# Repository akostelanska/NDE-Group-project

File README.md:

# NDE-Group-project
Repository for MPA-NDE Group Project

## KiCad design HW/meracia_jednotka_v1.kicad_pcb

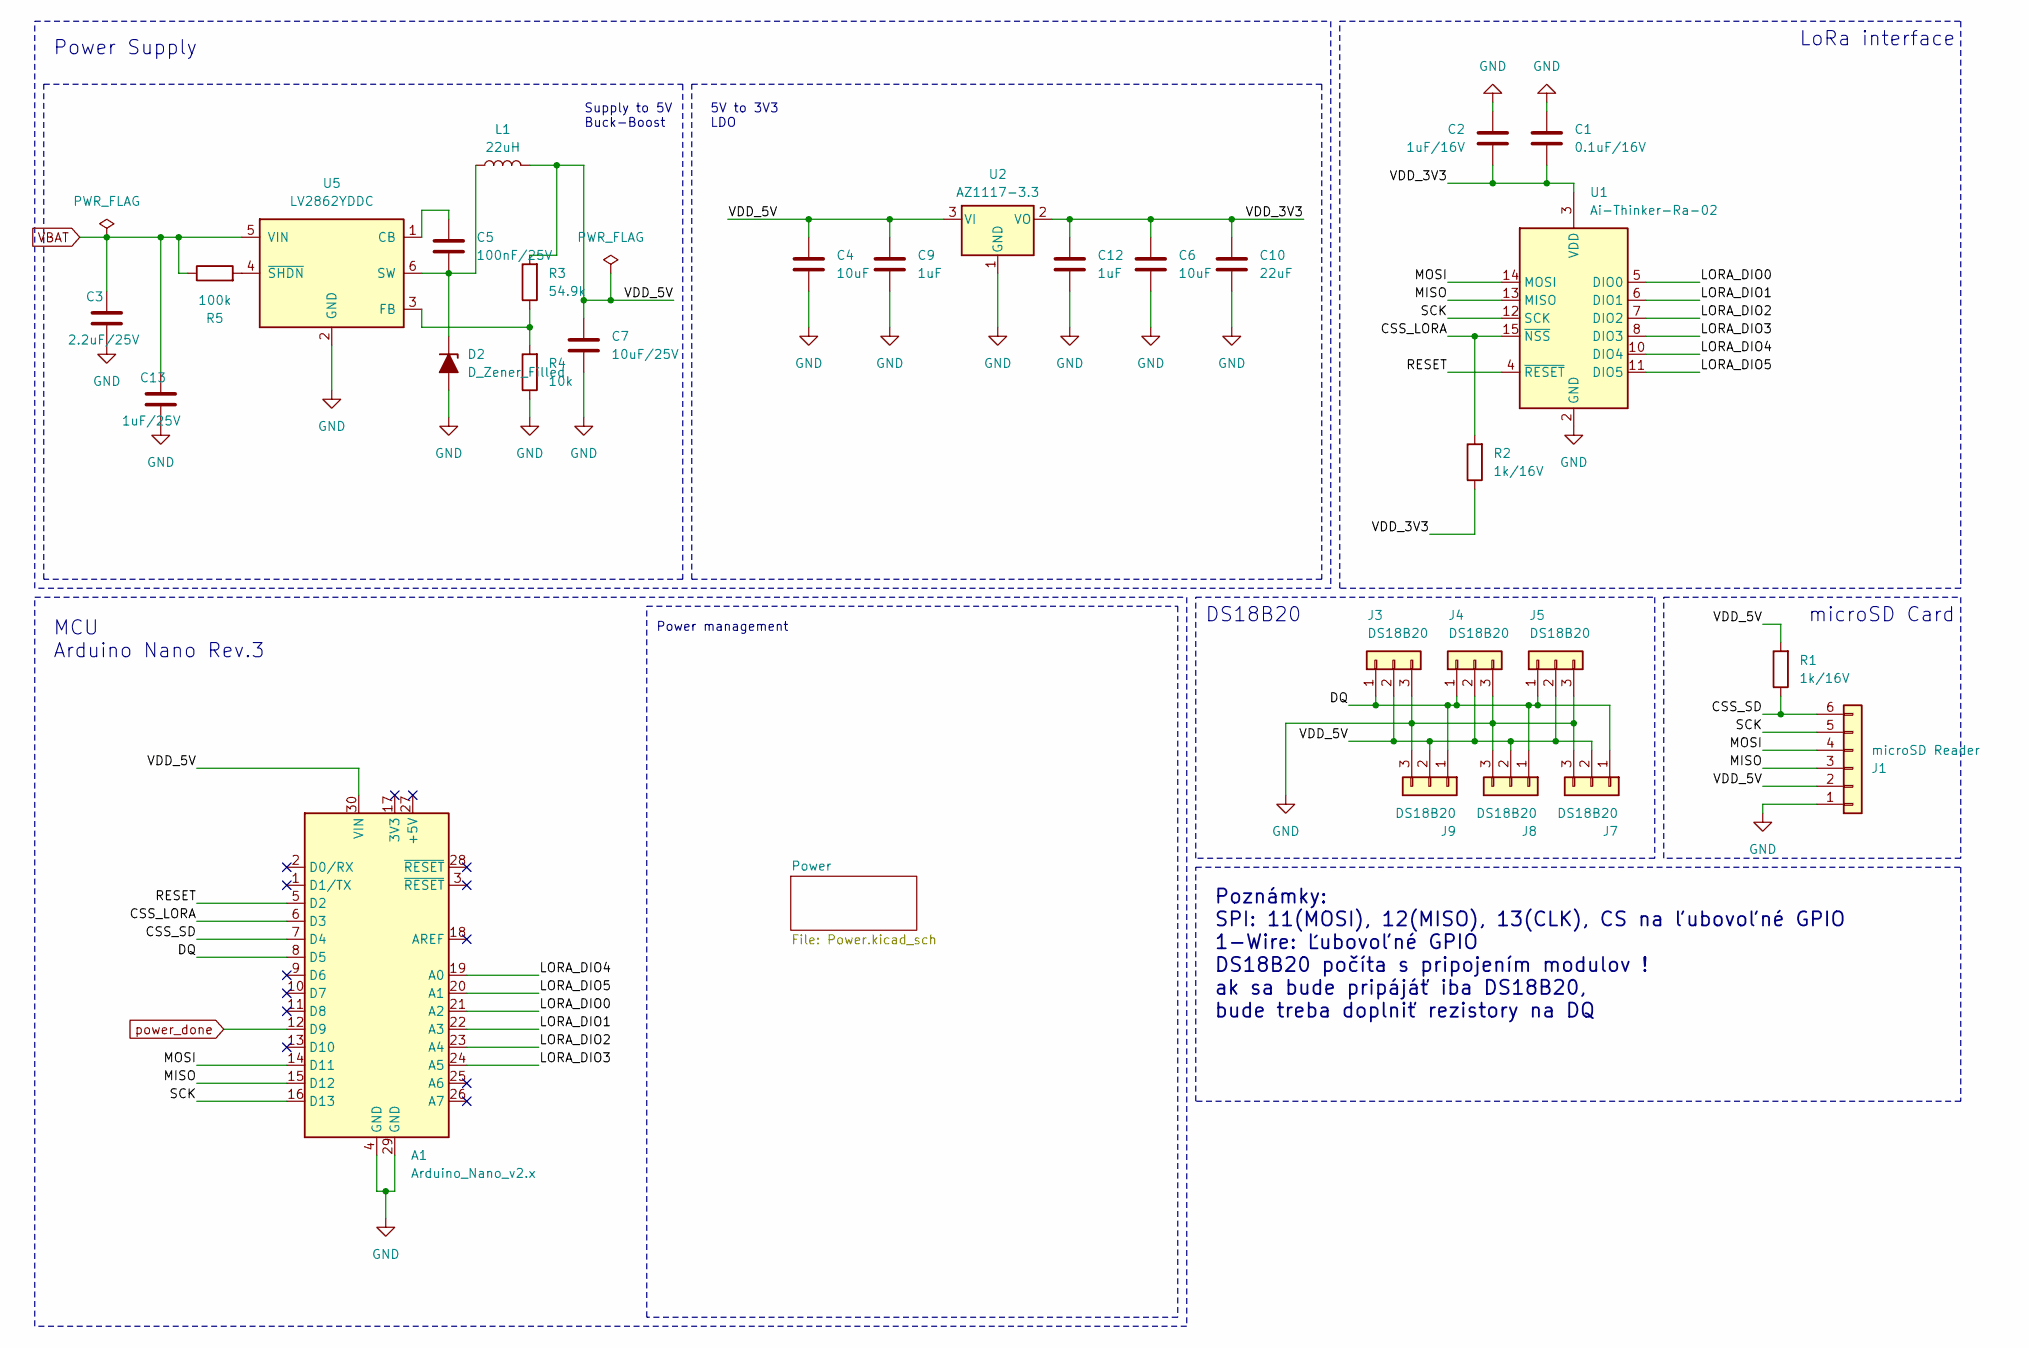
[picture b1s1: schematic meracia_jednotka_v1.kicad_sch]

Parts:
A1: Arduino_Nano_v2.x; Arduino_Nano
C1: 0.1uF/16V; C_1206_3216Metric_Pad1.33x1.80mm_HandSolder
C2: 1uF/16V; C_1206_3216Metric_Pad1.33x1.80mm_HandSolder
C3: 2.2uF/25V; C_1206_3216Metric_Pad1.33x1.80mm_HandSolder
C4, C6: 10uF; C_1206_3216Metric_Pad1.33x1.80mm_HandSolder
C5: 100nF/25V; C_1206_3216Metric_Pad1.33x1.80mm_HandSolder
C7: 10uF/25V; C_1206_3216Metric_Pad1.33x1.80mm_HandSolder
C9, C12: 1uF; C_0805_2012Metric_Pad1.18x1.45mm_HandSolder
C10: 22uF; C_1206_3216Metric_Pad1.33x1.80mm_HandSolder
C13: 1uF/25V; C_0805_2012Metric_Pad1.18x1.45mm_HandSolder
D2: D_Zener_Filled; D_1206_3216Metric_Pad1.42x1.75mm_HandSolder
J1: microSD Reader; PinHeader_1x06_P2.54mm_Vertical
J3, J4, J5, J7, J8, J9: DS18B20; PinHeader_1x03_P2.54mm_Vertical
L1: 22uH; L_Murata_LQH55DN_5.7x5.0mm
R1, R2: 1k/16V; R_1206_3216Metric_Pad1.30x1.75mm_HandSolder
R3: 54.9k; R_1206_3216Metric_Pad1.30x1.75mm_HandSolder
R4: 10k; R_1206_3216Metric_Pad1.30x1.75mm_HandSolder
R5: 100k; R_1206_3216Metric_Pad1.30x1.75mm_HandSolder
U1: Ai-Thinker-Ra-02; Ai-Thinker-Ra-01-LoRa
U2: AZ1117-3.3; SOT-223-3_TabPin2
U5: LV2862YDDC; SOT-23-6

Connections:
/CSS_LORA: A1.6 (D3), R2.2, U1.15 (~NSS)
/CSS_SD: A1.7 (D4), J1.6, R1.1
/DQ: A1.8 (D5), J3.1, J4.1, J5.1, J7.1, J8.1, J9.1
/LORA_DIO0: A1.21 (A2), U1.5 (DIO0)
/LORA_DIO1: A1.22 (A3), U1.6 (DIO1)
/LORA_DIO2: A1.23 (A4), U1.7 (DIO2)
/LORA_DIO3: A1.24 (A5), U1.8 (DIO3)
/LORA_DIO4: A1.19 (A0), U1.10 (DIO4)
/LORA_DIO5: A1.20 (A1), U1.11 (DIO5)
/MISO: A1.15 (D12), J1.3, U1.13 (MISO)
/MOSI: A1.14 (D11), J1.4, U1.14 (MOSI)
/RESET: A1.5 (D2), U1.4 (~RESET)
/SCK: A1.16 (D13), J1.5, U1.12 (SCK)
/VDD_3V3: C1.2, C2.2, C6.1, C10.1, C12.1, R2.1, U1.3 (VDD), U2.2 (VO)
/VDD_5V: A1.30 (VIN), C4.1, C7.1, C9.1, J1.2, J3.2, J4.2, J5.2, J7.2, J8.2, J9.2, L1.2, R1.2, R3.2, U2.3 (VI)
GND: A1.4 (GND), A1.29 (GND), C1.1, C2.1, C3.2, C4.2, C6.2, C7.2, C9.2, C10.2, C12.2, C13.2, D2.2 (A), J1.1, J3.3, J4.3, J5.3, J7.3, J8.3, J9.3, R4.1, U1.1 (GND), U1.2 (GND), U1.9 (GND), U1.16 (GND), U2.1 (GND), U5.2 (GND); also elsewhere on the board
unnamed: C5.2, D2.1 (K), L1.1, U5.6 (SW)
unnamed: C5.1, U5.1 (CB)
unnamed: R3.1, R4.2, U5.3 (FB)
unnamed: R5.2, U5.4 (~SHDN)
VBAT: C3.1, C13.1, R5.1, U5.5 (VIN); also elsewhere on the board
power_done: A1.12 (D9); also elsewhere on the board

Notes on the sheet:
5V to 3V3 LDO
Poznámky: SPI: 11(MOSI), 12(MISO), 13(CLK), CS na ľubovoľné GPIO 1-Wire: Ľubovoľné GPIO DS18B20 počíta s pripojením modulov ! ak sa bude pripájáť iba DS18B20, bude treba doplniť rezistory na DQ
Supply to 5V Buck-Boost
Power Supply
LoRa interface
MCU Arduino Nano Rev.3
microSD Card
Power management
DS18B20

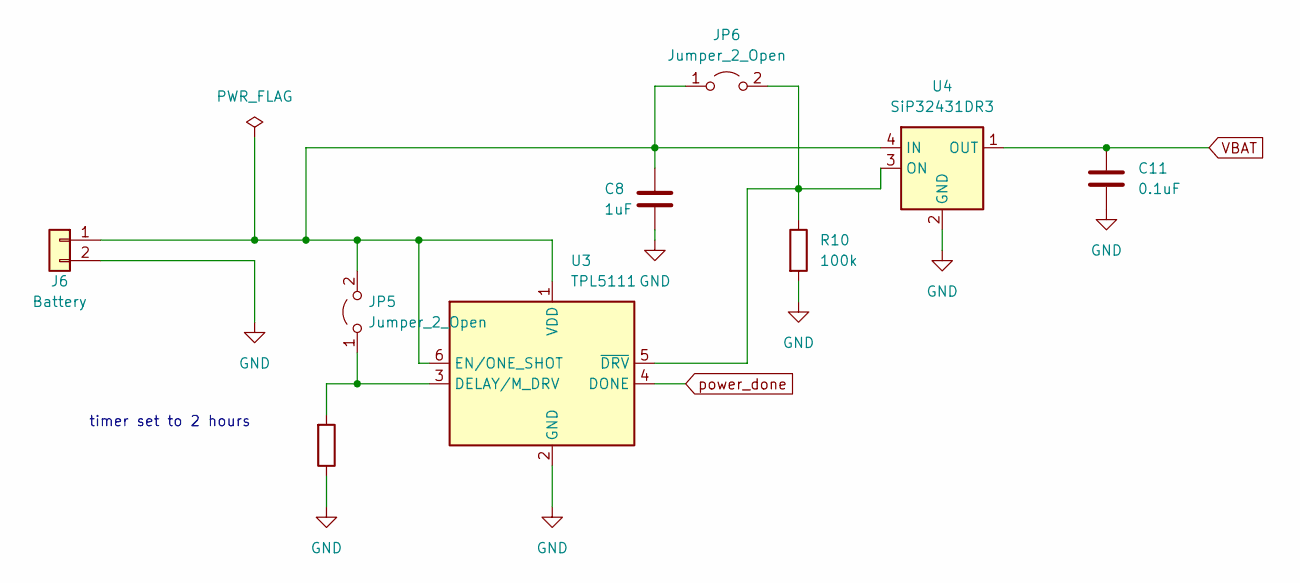
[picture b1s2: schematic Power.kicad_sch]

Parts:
C8: 1uF; C_1206_3216Metric_Pad1.33x1.80mm_HandSolder
C11: 0.1uF; C_1206_3216Metric_Pad1.33x1.80mm_HandSolder
J6: Battery; BatteryHolder_Keystone_2462_2xAA
JP5, JP6: Jumper_2_Open; PinHeader_1x02_P2.54mm_Vertical
R9: 57k; R_1206_3216Metric_Pad1.30x1.75mm_HandSolder
R10: 100k; R_1206_3216Metric_Pad1.30x1.75mm_HandSolder
U3: TPL5111; SOT-23-6
U4: SiP32431DR3; SOT-363_SC-70-6

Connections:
GND: C8.1, C11.2, J6.2, R9.1, R10.2, U3.2 (GND), U4.2 (GND), U4.5 (GND); also elsewhere on the board
unnamed: C8.2, J6.1, JP5.2 (B), JP6.1 (A), U3.1 (VDD), U3.6 (EN/ONE_SHOT), U4.4 (IN)
unnamed: JP5.1 (A), R9.2, U3.3 (DELAY/M_DRV)
unnamed: JP6.2 (B), R10.1, U3.5 (~DRV), U4.3 (ON)
VBAT: C11.1, U4.1 (OUT); also elsewhere on the board
power_done: U3.4 (DONE); also elsewhere on the board

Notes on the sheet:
timer set to 2 hours

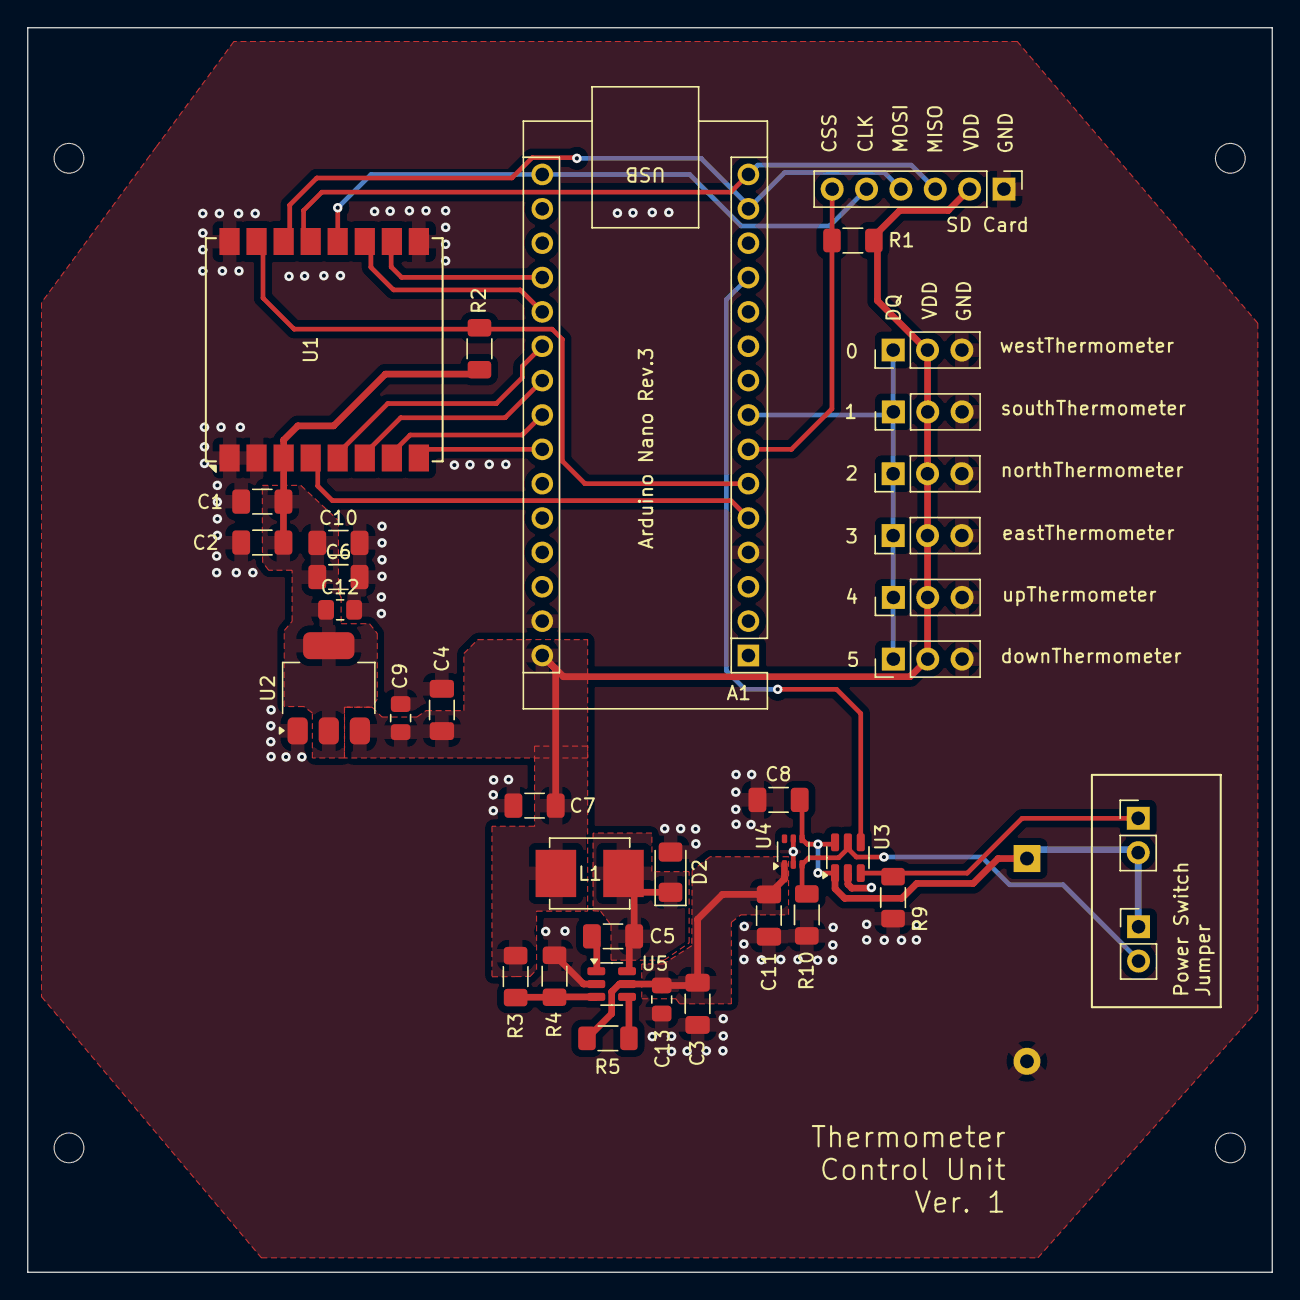
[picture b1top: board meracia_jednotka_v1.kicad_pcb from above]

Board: 2 copper layers, 92.0 x 92.0 mm, 38 parts (1 on the bottom side), 25 nets.

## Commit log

2024-02-26 Add files via upload
    initial commit
2024-03-05 Add files via upload
    LDO added
2024-03-05 Add files via upload
    dokumentácia
2024-03-13 Add files via upload
    napajanie vzor
2024-03-13 Create MPA-NDE
2024-03-13 MPA-NDE
2024-03-19 Add files via upload
    layout update
2024-03-20 skola 20.03.
